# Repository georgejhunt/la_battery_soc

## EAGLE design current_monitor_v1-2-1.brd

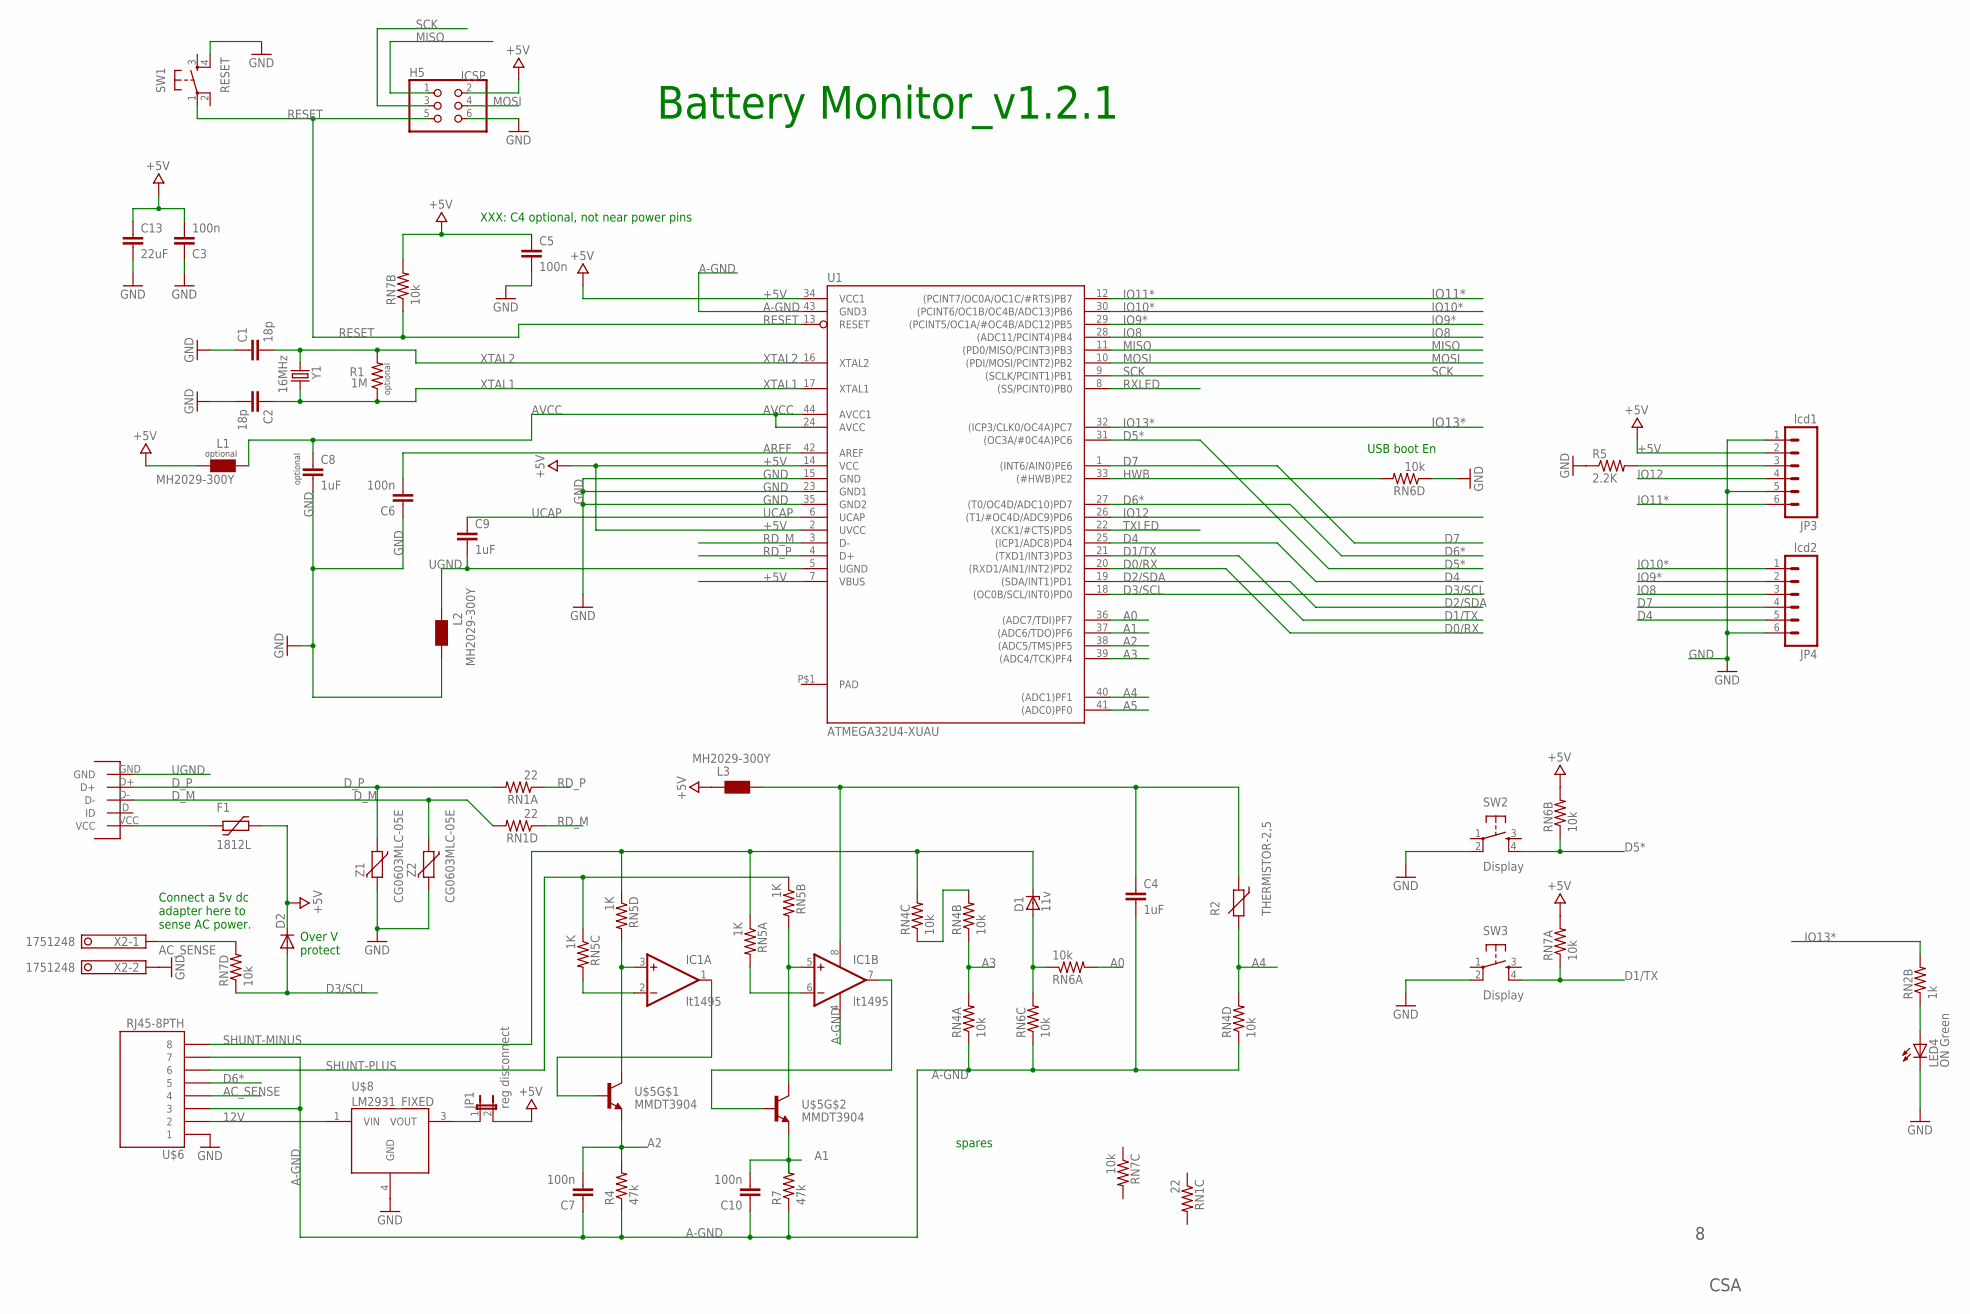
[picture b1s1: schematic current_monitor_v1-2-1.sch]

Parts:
C1, C2: 18p; 0805
C3, C5, C6, C7, C10: 100n; 0805
C4, C8, C9: 1uF; 0805
C13: 22uF; 1206
D1: 11v; ZDIO-5
D2: DIODESMA; SMA-DIODE
F1: 1812L
H5: ICSP; 2X03
IC1: lt1495; SO08
JP1: reg disconnect; 1X02_LOCK
JP3: lcd1; 1X06_FEMALE_LOCK.010
JP4: lcd2; 1X06_FEMALE_LOCK.010
L1, L2, L3: MH2029-300Y; 0805
LED4: ON Green; LED0805
R1: 1M; 0805
R2: THERMISTOR-2,5; RS-2,5
R4, R7: 47k; 0805
R5: 2.2K; 0805
RN1: 22; CRA06S
RN2: 1k; CRA06S
RN4, RN6, RN7: 10k; CRA06S
RN5: 1K; CRA06S
SW1: RESET; TACTILE-PTH
SW2, SW3: Display; TACTILE-PTH
U1: ATMEGA32U4-XUAU; TQFP44-PAD
U$5: MMDT3904; SOT363
U$6: RJ45-8PTH; RJ45-8
U$8: LM2931_FIXED; DPAK
U$16: USB-MICRO-B-DIGIKEY
X2: 1751248
Y1: 16MHz; HC49US
Z1, Z2: CG0603MLC-05E; CT/CN0603

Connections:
12V: U$6.2, U$8.1 (VIN)
+5V: C3.2, C5.1, C13.1, D2.C, F1.P$2 (2), H5.2, JP1.2, JP3.2, L1.1, L3.1, RN6.7 (2), RN7.7 (2), RN7.8 (2), U1.2 (UVCC), U1.7 (VBUS), U1.14 (VCC), U1.34 (VCC1)
A0: RN6.8 (2), U1.36 ((ADC7/TDI)PF7)
A1: C10.2, R7.2, U1.37 ((ADC6/TDO)PF6), U$5.1 (E)
A2: C7.2, R4.2, U1.38 ((ADC5/TMS)PF5), U$5.4 (E)
A3: RN4.2 (1), RN4.8 (2), U1.39 ((ADC4/TCK)PF4)
A4: R2.2, RN4.5 (2), U1.40 ((ADC1)PF1)
A5: U1.41 ((ADC0)PF0)
A-GND: C4.2, C7.1, C10.1, IC1.4 (V-), R4.1, R7.1, RN4.1, RN4.4 (1), RN6.3 (1), U1.43 (GND3), U$6.3, U$6.7
AC_SENSE: RN7.5 (2), U$6.4, X2.1
AREF: C6.2, U1.42 (AREF)
AVCC: C8.1, L1.2, U1.24 (AVCC), U1.44 (AVCC1)
D0/RX: U1.20 ((RXD1/AIN1/INT2)PD2)
D1/TX: RN7.1, SW3.4, U1.21 ((TXD1/INT3)PD3)
D2/SDA: U1.19 ((SDA/INT1)PD1)
D3/SCL: D2.A, RN7.4 (1), U1.18 ((OC0B/SCL/INT0)PD0)
D4: JP4.5, U1.25 ((ICP1/ADC8)PD4)
D5*: RN6.2 (1), SW2.4, U1.31 ((OC3A/#0C4A)PC6)
D6*: U1.27 ((T0/OC4D/ADC10)PD7), U$6.5
D7: JP4.4, U1.1 ((INT6/AIN0)PE6)
D_M: RN1.5 (2), U$16.D-, Z2.1
D_P: RN1.8 (2), U$16.D+, Z1.1
GND: C1.1, C2.2, C3.1, C5.2, C6.1, C8.2, C13.2, H5.6, JP3.1, JP3.5, JP4.6, L2.2, LED4.C, R5.1, RN6.4 (1), SW1.4, SW2.2, SW3.2, U1.15 (GND), U1.23 (GND1), U1.35 (GND2), U$6.1, U$8.4 (GND), X2.2, Z1.2, Z2.2
HWB: RN6.5 (2), U1.33 ((#HWB)PE2)
IO8: JP4.3, U1.28 ((ADC11/PCINT4)PB4)
IO9*: JP4.2, U1.29 ((PCINT5/OC1A/#OC4B/ADC12)PB5)
IO10*: JP4.1, U1.30 ((PCINT6/OC1B/OC4B/ADC13)PB6)
IO11*: JP3.6, U1.12 ((PCINT7/OC0A/OC1C/#RTS)PB7)
IO12: JP3.4, U1.26 ((T1/#OC4D/ADC9)PD6)
IO13*: RN2.7 (2), U1.32 ((ICP3/CLK0/OC4A)PC7)
LED4_ANODE: LED4.A, RN2.2 (1)
MISO: H5.1, U1.11 ((PD0/MISO/PCINT3)PB3)
MOSI: H5.4, U1.10 ((PDI/MOSI/PCINT2)PB2)
unnamed: IC1.5 (+IN), RN5.7 (2), U$5.6 (C)
unnamed: IC1.2 (-IN), RN5.6 (2)
unnamed: IC1.6 (-IN), RN5.8 (2)
unnamed: IC1.1 (OUT), U$5.5 (B)
unnamed: IC1.7 (OUT), U$5.2 (B)
unnamed: IC1.3 (+IN), RN5.5 (2), U$5.3 (C)
unnamed: F1.P$1 (1), U$16.VCC
unnamed: JP1.1, U$8.3 (VOUT)
unnamed: RN4.3 (1), RN4.7 (2)
unnamed: JP3.3, R5.2
unnamed: D1.A, RN6.1, RN6.6 (2)
unnamed: C4.1, IC1.8 (V+), L3.2, R2.1
PAD: U1.P$1 (PAD)
RD_M: RN1.4 (1), U1.3 (D-)
RD_P: RN1.1, U1.4 (D+)
RESET: H5.5, RN7.2 (1), SW1.1, U1.13 (RESET)
RXLED: U1.8 ((SS/PCINT0)PB0)
SCK: H5.3, U1.9 ((SCLK/PCINT1)PB1)
SHUNT-MINUS: D1.C, RN4.6 (2), RN5.1, RN5.4 (1), U$6.8
SHUNT-PLUS: RN5.2 (1), RN5.3 (1), U$6.6
TXLED: U1.22 ((XCK1/#CTS)PD5)
UCAP: C9.1, U1.6 (UCAP)
UGND: C9.2, L2.1, U1.5 (UGND), U$16.GND
XTAL1: C2.1, R1.1, U1.17 (XTAL1), Y1.2
XTAL2: C1.2, R1.2, U1.16 (XTAL2), Y1.1

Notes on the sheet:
Battery Monitor_v1.2.1
USB boot En
optional
CSA
XXX: C4 optional, not near power pins
spares
Connect a 5v dc adapter here to sense AC power.
Over V protect

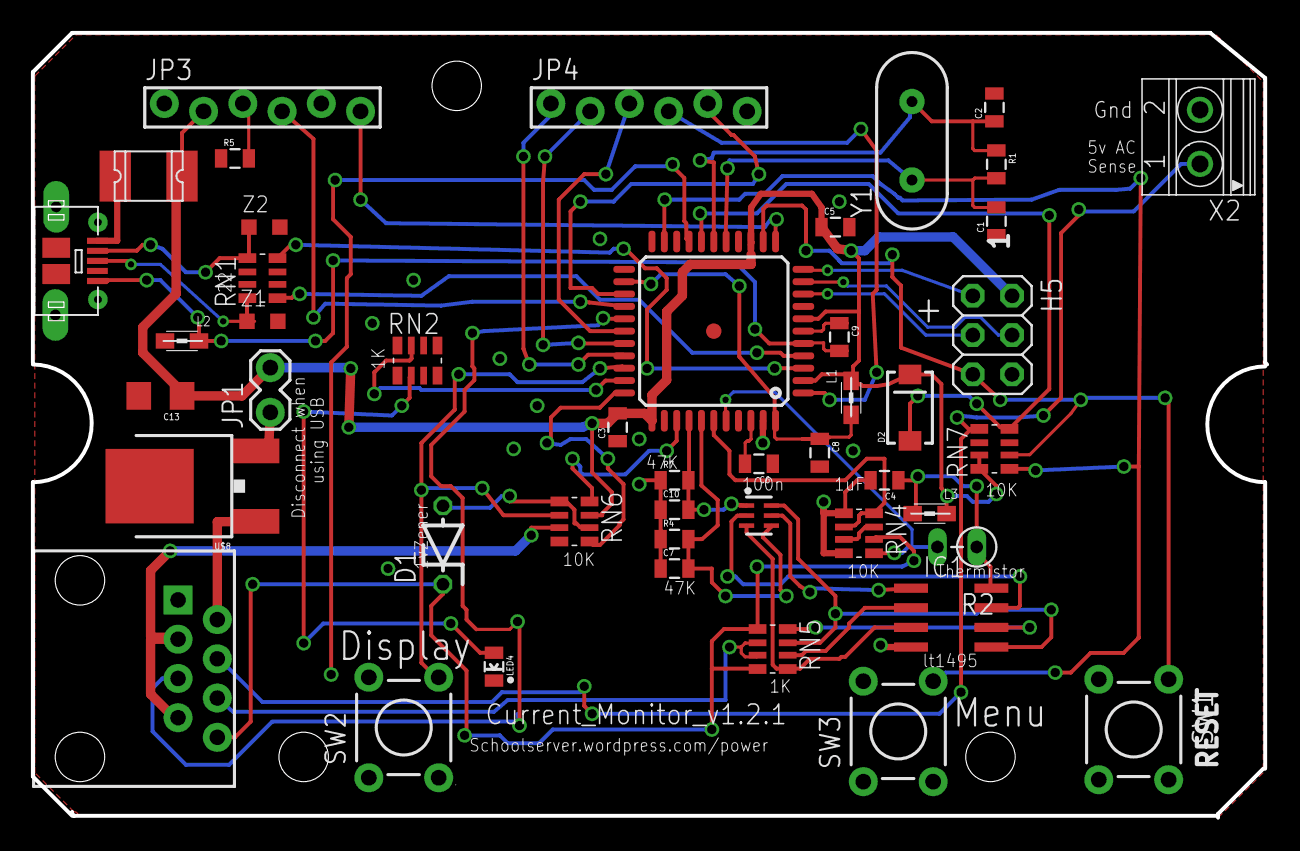
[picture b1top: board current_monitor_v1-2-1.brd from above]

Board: 2 copper layers, 79.9 x 50.8 mm, 46 parts (0 on the bottom side), 52 nets.

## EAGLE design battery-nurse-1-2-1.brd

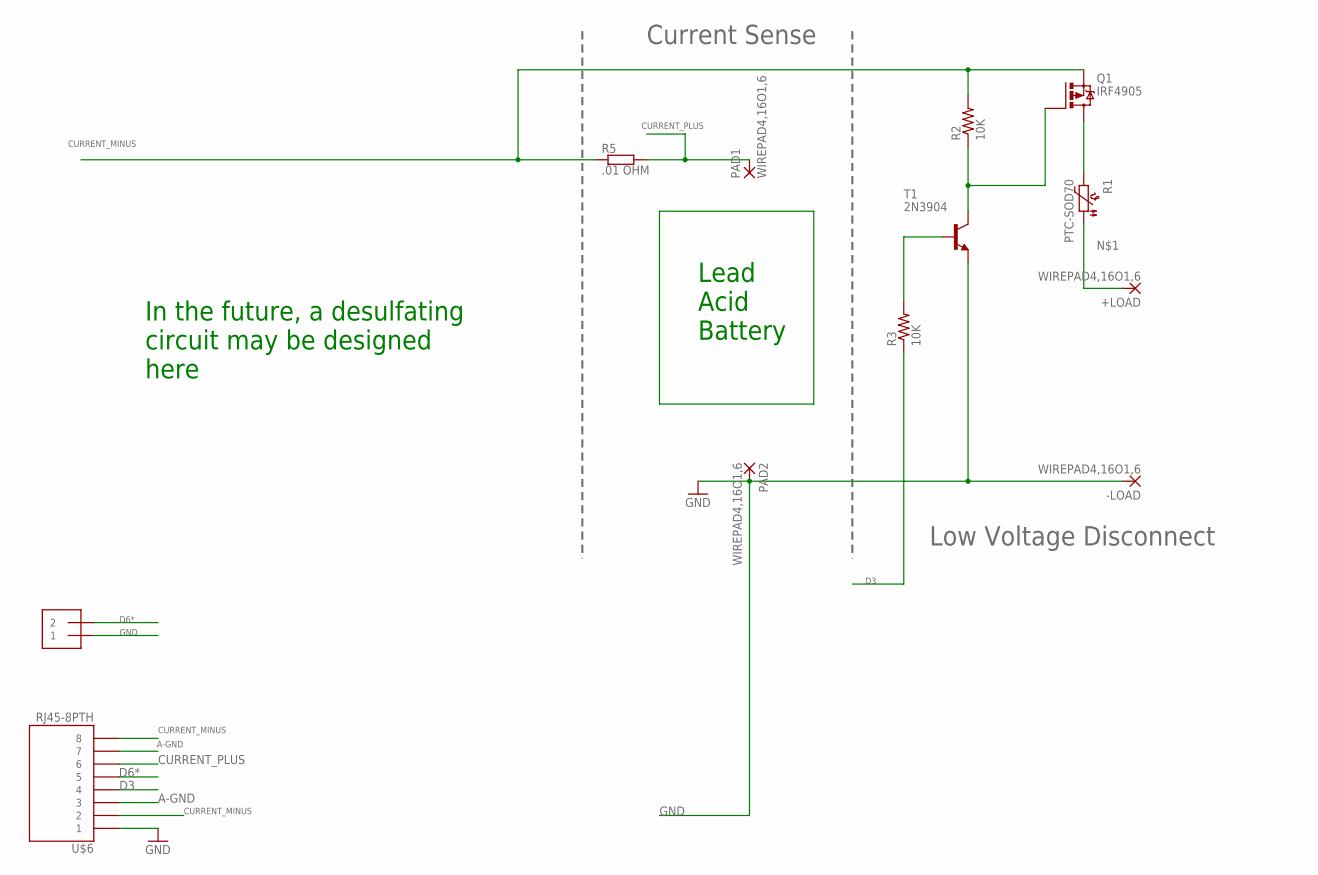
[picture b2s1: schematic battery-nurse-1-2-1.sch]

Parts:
+LOAD: WIREPAD4,16O1,6; 4,16O1,6
-LOAD: WIREPAD4,16O1,6; 4,16O1,6
J1: 1X2-3.5MM
PAD1, PAD2: WIREPAD4,16O1,6; 4,16O1,6
Q1: IRF4905; TO220BH
R1: PTC-SOD70; SOD70
R2, R3: 10K; 0204/7
R5: .01 OHM; SMT-REF
T1: 2N3904; TO92-EBC-OVAL
U$6: RJ45-8PTH; RJ45-8

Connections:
A-GND: U$6.3, U$6.7
CURRENT_MINUS: Q1.S, R2.2, R5.2, U$6.2, U$6.8
CURRENT_PLUS: PAD1.1, R5.1, U$6.6
D3: R3.1, U$6.4
D6*: J1.2, U$6.5
GND: -LOAD.1, J1.1, PAD2.1, T1.E, U$6.1
unnamed: +LOAD.1, R1.1
unnamed: Q1.D, R1.2
unnamed: Q1.G, R2.1, T1.C
unnamed: R3.2, T1.B

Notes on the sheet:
Lead Acid Battery
Low Voltage Disconnect
Current Sense
In the future, a desulfating circuit may be designed here

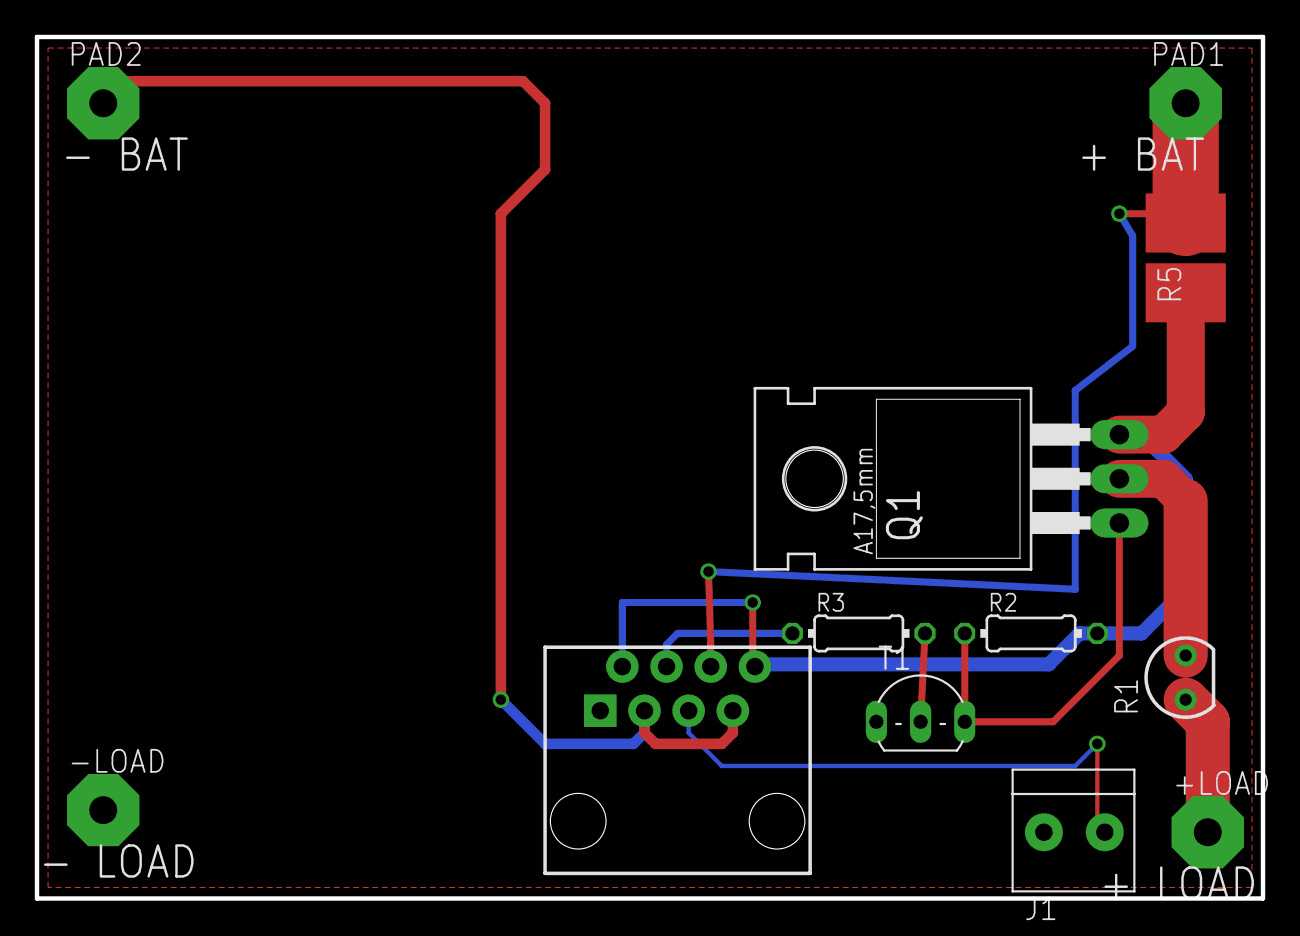
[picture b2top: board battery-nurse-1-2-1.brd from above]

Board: 2 copper layers, 70.5 x 49.5 mm, 12 parts (0 on the bottom side), 10 nets.

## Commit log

2014-06-30 checkin just selected stuff from xorduino
2014-07-17 version1.2.1 as submitted for pcb fab

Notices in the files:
parts and their libraries:
SparkFun-Connectors: Licensing: CC v3.0 Share-Alike You are welcome to use this library for commercial purposes.
